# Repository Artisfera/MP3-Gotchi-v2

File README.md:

# MP3-Gotchi v2

A pocket-sized offline MP3 player with a Tamagotchi-style monkey companion, being developed around a custom ESP32-S3 PCB.

## Original version (v1)

## Why?

Have you ever lost signal during a trip and realised that streaming had quietly become your entire music library?

You can store MP3 files on a phone, of course, but carrying a dedicated music player still feels different.

My girlfriend runs into this problem often, so for our anniversary I decided to build her a one-of-a-kind Tamagotchi-style MP3 player. While listening to music, she will also be able to feed and take care of a little monkey companion.

She loves monkeys, so it fits perfectly ✨

## What makes v2 different?

The first MP3-Gotchi proved that the idea could work, but it was built mostly from ready-made development modules. That made the device larger, limited the available hardware choices and left many parts of the design hidden inside separate boards.

Version 2 is being rebuilt around a custom ESP32-S3 PCB. Instead of connecting complete modules together, the main parts of the player are being designed directly into one compact device.

The new version is planned to include:

- offline music playback from a microSD card
- a dedicated stereo DAC and headphone amplifier
- support for wired TRRS headphones and their microphone
- a small internal speaker
- a 96×64 color OLED
- motion sensing
- dual vibration feedback
- a rotary encoder and physical buttons
- USB-C charging and programming
- a rechargeable Li-Ion battery

These are the goals for the complete v2 design. The current HomeFab prototype does not include every planned feature.

## Current status

> [!IMPORTANT]
> MP3-Gotchi v2 is under active hardware development. The version currently available in this repository is **HomeFab v0.1.0**, a reduced PCB design intended for experimental home fabrication. The full version for professional PCB manufacturing is a future development step. The board has not been documented here as manufactured and hardware-tested.

### HomeFab v0.1.0

The HomeFab revision omits microphone support, the dedicated battery over-discharge protection circuit, and the second vibration motor. These are still part of the intended full v2 design.

| Block | Component | HomeFab v0.1.0 status |
| --- | --- | --- |
| USB-C | USB-C receptacle | Included in schematic |
| Battery charger | TP4056 | Included in schematic |
| Battery connection | Li-Ion cell connector | Included in schematic |
| Battery protection | DW01A + FS8205A | Not included in HomeFab |
| 3.3 V buck converter | SC189ZSKTRT | Included in schematic |
| Microcontroller | ESP32-S3-WROOM | Included in schematic |
| Stereo DAC | PCM5102A | Included in schematic |
| Headphone amplifier | TS482IDT | Included in schematic |
| Microphone preamp | TLV9062 | Not included in HomeFab |
| TRRS headphone jack | FC68129 | Included; microphone circuitry omitted |
| microSD socket | ATTEND 112I-TA01 | Included in schematic |
| Rotary encoder | Encoder with push switch | Included in schematic |
| Vibration motors | Mini vibration motor | One included; second omitted |
| 6-axis IMU | MPU6050 | Included in schematic |
| Color OLED | SSD1331, 96×64 | Separate module, connected to main PCB |
| Internal speaker amplifier | PAM8302AAD | Included in schematic |
| Buttons | Two user buttons | Included in schematic |

**Project files:** [HomeFab KiCad project](hardware/MP3-Gotchi-v2_HomeFab/) | [HomeFab BOM (CSV)](hardware/MP3-Gotchi-v2_HomeFab/MP3-Gotchi-v2_HomeFab.csv) | [Historical revision exports](hardware/reversions/)

The BOM is located in the HomeFab directory. It is a working component and purchasing list, not yet a verified manufacturing BOM. Some entries still refer to components omitted from the current HomeFab schematic and need to be reconciled before ordering PCB assembly.

## Development journal

The project is being documented from the first hardware decisions to the final physical build. The journal includes design choices, mistakes, revisions and timelapses from each development session.

[Read the development journal](JOURNAL.md)

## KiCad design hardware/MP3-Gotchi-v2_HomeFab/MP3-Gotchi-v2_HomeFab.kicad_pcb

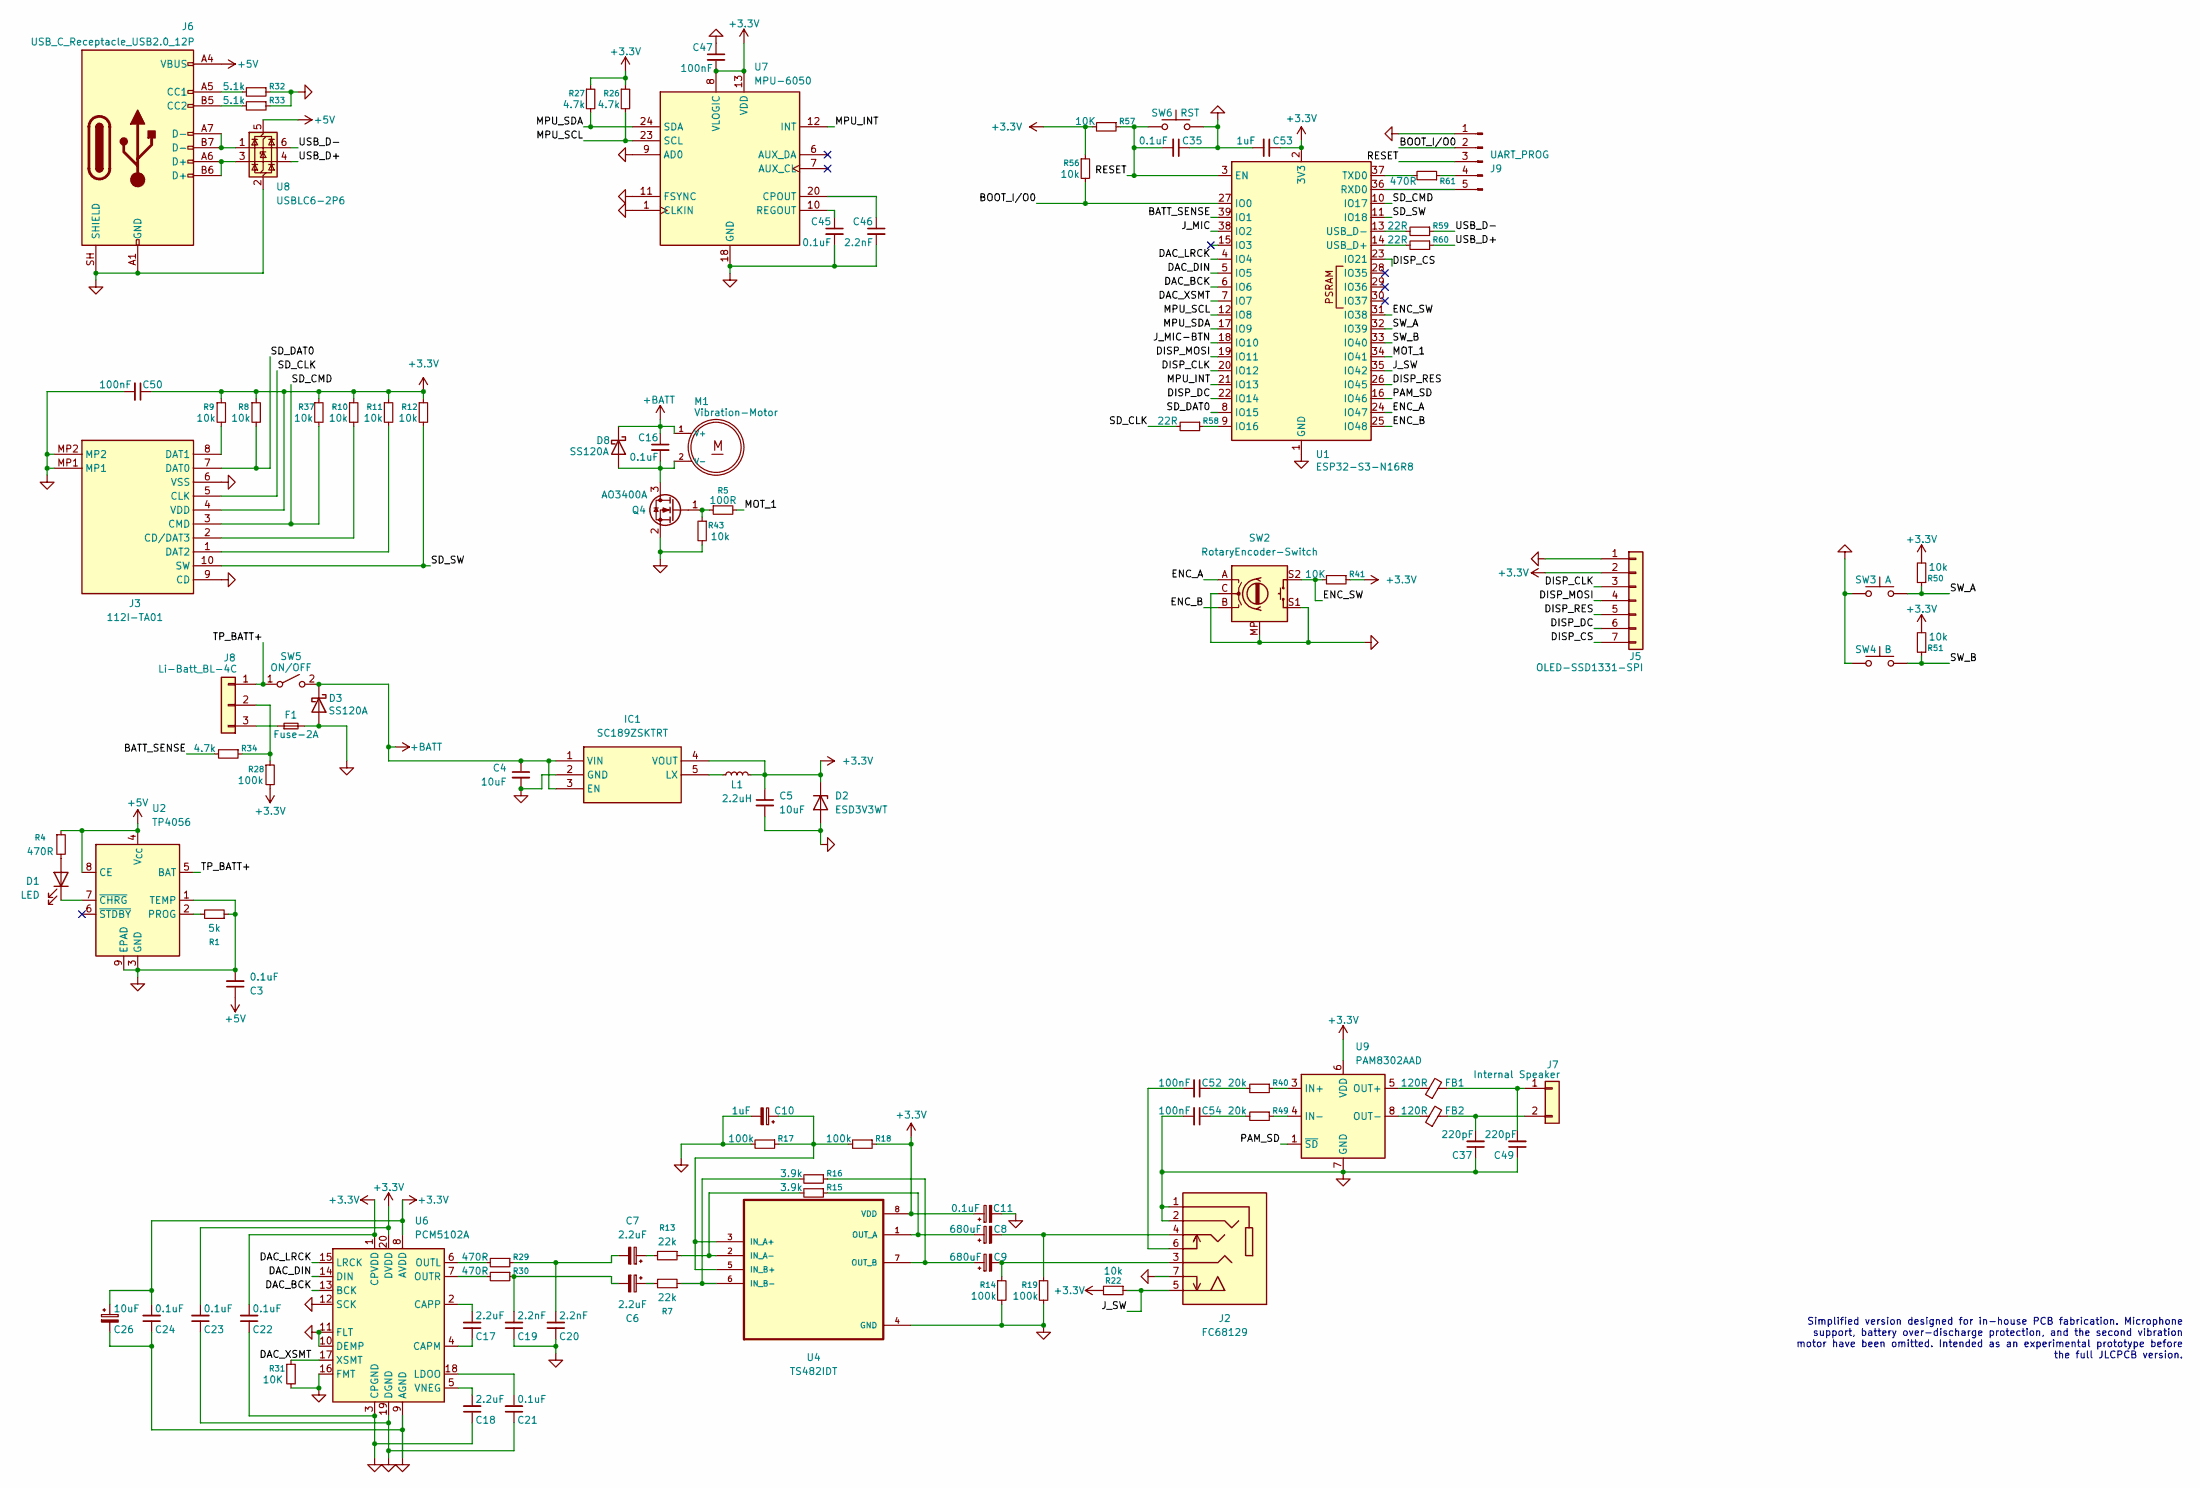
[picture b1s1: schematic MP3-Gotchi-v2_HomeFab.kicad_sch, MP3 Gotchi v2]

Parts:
C3, C11, C16, C21, C22, C23, C24, C45: 0.1uF; C_0402_1005Metric_Pad0.74x0.62mm_HandSolder
C4, C5, C26: 10uF; C_0805_2012Metric_Pad1.18x1.45mm_HandSolder
C6, C7, C17, C18: 2.2uF; C_0805_2012Metric_Pad1.18x1.45mm_HandSolder
C8, C9: 680uF; C_Elec_8x10.2
C10: 1uF; C_0805_2012Metric_Pad1.18x1.45mm_HandSolder
C19, C20, C46: 2.2nF; C_0603_1608Metric_Pad1.08x0.95mm_HandSolder
C35: 0.1uF; C_0805_2012Metric_Pad1.18x1.45mm_HandSolder
C37, C49: 220pF; C_0603_1608Metric_Pad1.08x0.95mm_HandSolder
C47, C50: 100nF; C_0603_1608Metric_Pad1.08x0.95mm_HandSolder
C52, C54: 100nF; C_1206_3216Metric_Pad1.33x1.80mm_HandSolder
C53: 1uF; C_0805_2012Metric
D1: LED; LED_0603_1608Metric_Pad1.05x0.95mm_HandSolder
D2: ESD3V3WT; D_SOD-523
D3, D8: SS120A; D_SMA
F1: Fuse-2A; Fuse_1206_3216Metric_Pad1.42x1.75mm_HandSolder
FB1, FB2: 120R; R_0603_1608Metric_Pad0.98x0.95mm_HandSolder
IC1: SC189ZSKTRT; SOT-753; Manufacturer_Part_Number SC189ZSKTRT
J2: FC68129; AudioJack_Cliff_FC68129
J3: 112I-TA01; ATTEND_112I-TA01; Manufacturer_Part_Number 112I-TA01
J5: OLED-SSD1331-SPI; JST_XH_B7B-XH-A_1x07_P2.50mm_Vertical
J6: USB_C_Receptacle_USB2.0_12P; USB_C_Receptacle_HRO_TYPE-C-31-M-12
J7: Internal Speaker; JST_PH_B2B-PH-K_1x02_P2.00mm_Vertical
J8: Li-Batt_BL-4C; JST_PH_B3B-PH-K_1x03_P2.00mm_Vertical
J9: UART_PROG; PinHeader_1x05_P2.54mm_Vertical
L1: 2.2uH; L_Wuerth_PMFI-252012
M1: Vibration-Motor; JST_PH_B2B-PH-K_1x02_P2.00mm_Vertical
Q4: AO3400A; SOT-23
R1: 5k; R_0603_1608Metric_Pad0.98x0.95mm_HandSolder
R4, R29, R30, R61: 470R; R_0603_1608Metric_Pad0.98x0.95mm_HandSolder
R5: 100R; R_0603_1608Metric_Pad0.98x0.95mm_HandSolder
R7, R13: 22k; R_0603_1608Metric_Pad0.98x0.95mm_HandSolder
R8, R9, R10, R11, R12, R22, R37, R43, R50, R51, R56: 10k; R_0603_1608Metric_Pad0.98x0.95mm_HandSolder
R14, R17, R18, R19, R28: 100k; R_0603_1608Metric_Pad0.98x0.95mm_HandSolder
R15, R16: 3.9k; R_0603_1608Metric_Pad0.98x0.95mm_HandSolder
R26, R27, R34: 4.7k; R_0603_1608Metric_Pad0.98x0.95mm_HandSolder
R31, R41, R57: 10K; R_0603_1608Metric_Pad0.98x0.95mm_HandSolder
R32, R33: 5.1k; R_0603_1608Metric_Pad0.98x0.95mm_HandSolder
R40, R49: 20k; R_0603_1608Metric_Pad0.98x0.95mm_HandSolder
R58, R59, R60: 22R; R_0603_1608Metric_Pad0.98x0.95mm_HandSolder
SW2: RotaryEncoder-Switch; RotaryEncoder_Alps_EC11E-Switch_Vertical_H20mm
SW3: A; Switch_Tactile_SMD_6x6mm
SW4: B; Switch_Tactile_SMD_6x6mm
SW5: ON/OFF; JST_PH_B2B-PH-K_1x02_P2.00mm_Vertical
SW6: RST; SolderJumper-2_P1.3mm_Open_RoundedPad1.0x1.5mm
U1: ESP32-S3-N16R8; ESP32-S3-WROOM-1
U2: TP4056; SOIC-8-1EP_3.9x4.9mm_P1.27mm_EP2.41x3.3mm_ThermalVias
U4: TS482IDT; SOIC-8_3.9x4.9mm_P1.27mm
U6: PCM5102A; TSSOP-20_4.4x6.5mm_P0.65mm
U7: MPU-6050; InvenSense_QFN-24_4x4mm_P0.5mm
U8: USBLC6-2P6; SOT-666
U9: PAM8302AAD; SOIC-8_3.9x4.9mm_P1.27mm

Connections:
+3.3V: C5.1, C11.1, C22.2, C23.2, C24.2, C26.1, C47.2, C50.1, C53.1, D2.1 (K), IC1.4 (VOUT), J3.4 (VDD), J5.2, L1.2, R8.1, R9.1, R10.1, R11.1, R12.1, R18.1, R22.2, R26.1, R27.1, R28.2, R37.1, R41.1, R50.2, R51.2, R56.1, R57.2, U1.2 (3V3), U4.8 (VDD), U6.1 (CPVDD), U6.8 (AVDD), U6.20 (DVDD), U7.8 (VLOGIC), U7.13 (VDD), U9.6 (VDD)
+5V: C3.1, J6.A4 (VBUS), J6.A9 (VBUS), J6.B4 (VBUS), J6.B9 (VBUS), R4.1, U2.4 (V_{CC}), U2.8 (CE), U8.5 (VBUS)
+BATT: C4.1, C16.1, D3.1 (K), D8.1 (K), IC1.1 (VIN), IC1.3 (EN), M1.1 (V+), SW5.2 (B)
/BATT_SENSE: R34.2, U1.39 (IO1)
/BOOT_I/O0: J9.2, R56.2, U1.27 (IO0)
/DAC_BCK: U1.6 (IO6), U6.13 (BCK)
/DAC_DIN: U1.5 (IO5), U6.14 (DIN)
/DAC_LRCK: U1.4 (IO4), U6.15 (LRCK)
/DAC_XSMT: R31.1, U1.7 (IO7), U6.17 (XSMT)
/DISP_CLK: J5.3, U1.20 (IO12)
/DISP_CS: J5.7, U1.23 (IO21)
/DISP_DC: J5.6, U1.22 (IO14)
/DISP_MOSI: J5.4, U1.19 (IO11)
/DISP_RES: J5.5, U1.26 (IO45)
/ENC_A: SW2.A, U1.24 (IO47)
/ENC_B: SW2.B, U1.25 (IO48)
/ENC_SW: R41.2, SW2.S2 (S1), U1.31 (IO38)
/J_MIC: U1.38 (IO2)
/J_MIC-BTN: U1.18 (IO10)
/J_SW: J2.5 (SW_A), R22.1, U1.35 (IO42)
/MOT_1: R5.2, U1.34 (IO41)
/MOT_2: U1.15 (IO3)
/MPU_INT: U1.21 (IO13), U7.12 (INT)
/MPU_SCL: R26.2, U1.12 (IO8), U7.23 (SCL)
/MPU_SDA: R27.2, U1.17 (IO9), U7.24 (SDA)
/PAM_SD: U1.16 (IO46), U9.1 (~SD)
/RESET: C35.2, J9.3, R57.1, SW6.1, U1.3 (EN)
/SD_CLK: J3.5 (CLK), R58.2
/SD_CMD: J3.3 (CMD), R37.2, U1.10 (IO17)
/SD_DAT0: J3.7 (DAT0), R8.2, U1.8 (IO15)
/SD_SW: J3.10 (SW), R12.2, U1.11 (IO18)
/SW_A: R50.1, SW3.2, U1.32 (IO39)
/SW_B: R51.1, SW4.2, U1.33 (IO40)
/TP_BATT+: J8.1 (Pin_3), SW5.1 (A), U2.5 (BAT)
/USB_D+: R60.1, U8.4 (I/O2)
/USB_D-: R59.1, U8.6 (I/O1)
GND: C3.2, C4.2, C5.2, C10.2, C11.2, C18.1, C19.1, C20.1, C21.1, C22.1, C23.1, C24.1, C26.2, C35.1, C37.1, C45.2, C46.2, C47.1, C49.1, C50.2, C53.2, C54.2, D2.2 (A), D3.2 (A), F1.2, IC1.2 (GND), J2.1 (S), J2.2 (R1), J2.7 (SW_B), J3.6 (VSS), J3.9 (CD), J3.MP1, J3.MP2, J5.1, J6.A1 (GND), J6.A12 (GND), J6.B1 (GND), J6.B12 (GND), J6.SH (SHIELD), J9.1, Q4.2 (S), R1.1, R14.2, R17.2, R19.2, R31.2, R32.1, R33.1, R43.2, SW2.C, SW2.MP, SW2.S1 (S2), SW3.1, SW4.1, SW6.2, U1.1 (GND), U1.40 (GND), U1.41 (GND), U2.1 (TEMP), U2.3 (GND), U2.9 (EPAD), U4.4 (GND), U6.3 (CPGND), U6.9 (AGND), U6.10 (DEMP), U6.11 (FLT), U6.12 (SCK), U6.16 (FMT), U6.19 (DGND), U7.1 (CLKIN), U7.9 (AD0), U7.11 (FSYNC), U7.18 (GND), U8.2 (GND), U9.7 (GND)
unnamed: C6.1, R7.2
unnamed: C7.1, R13.2
unnamed: C6.2, C19.2, R30.1
unnamed: C7.2, C20.2, R29.1
unnamed: C52.1, R40.2
unnamed: C54.1, R49.2
unnamed: D1.2 (A), R4.2
unnamed: D1.1 (K), U2.7 (~CHRG)
unnamed: C16.2, D8.2 (A), M1.2 (V-), Q4.3 (D)
unnamed: IC1.5 (LX), L1.1
unnamed: C9.2, J2.3 (R2), R14.1
unnamed: C8.2, J2.4 (T), R19.1
unnamed: C52.2, J2.6 (T_SW)
unnamed: J3.2 (CD/DAT3), R10.2
unnamed: J3.8 (DAT1), R9.2
unnamed: J3.1 (DAT2), R11.2
unnamed: J6.A5 (CC1), R32.2
unnamed: J6.B5 (CC2), R33.2
unnamed: J6.A6 (D+), J6.B6 (D+), U8.3 (I/O2)
unnamed: J6.A7 (D-), J6.B7 (D-), U8.1 (I/O1)
unnamed: C37.2, FB2.2, J7.2 (Pin_1)
unnamed: C49.2, FB1.2, J7.1 (Pin_2)
unnamed: F1.1, J8.3 (Pin_1)
unnamed: J8.2, R28.1, R34.1
unnamed: J9.4, R61.1
unnamed: J9.5, U1.36 (RXD0)
unnamed: Q4.1 (G), R5.1, R43.1
unnamed: R58.1, U1.9 (IO16)
unnamed: R61.2, U1.37 (TXD0)
unnamed: R60.2, U1.14 (USB_D+)
unnamed: R59.2, U1.13 (USB_D-)
unnamed: R1.2, U2.2 (PROG)
unnamed: C10.1, R17.1, R18.2, U4.3 (IN_A+), U4.5 (IN_B+)
unnamed: R13.1, R15.2, U4.2 (IN_A-)
unnamed: R7.1, R16.2, U4.6 (IN_B-)
unnamed: C8.1, R15.1, U4.1 (OUT_A)
unnamed: C9.1, R16.1, U4.7 (OUT_B)
unnamed: C17.1, U6.4 (CAPM)
unnamed: C17.2, U6.2 (CAPP)
unnamed: C21.2, U6.18 (LDOO)
unnamed: R29.2, U6.6 (OUTL)
unnamed: R30.2, U6.7 (OUTR)
unnamed: C18.2, U6.5 (VNEG)
unnamed: C46.1, U7.20 (CPOUT)
unnamed: C45.1, U7.10 (REGOUT)
unnamed: R40.1, U9.3 (IN+)
unnamed: R49.1, U9.4 (IN-)
unnamed: FB1.1, U9.5 (OUT+)
unnamed: FB2.1, U9.8 (OUT-)

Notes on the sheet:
Simplified version designed for in-house PCB fabrication. Microphone support, battery over-discharge protection, and the second vibration motor have been omitted. Intended as an experimental prototype before the full JLCPCB version.

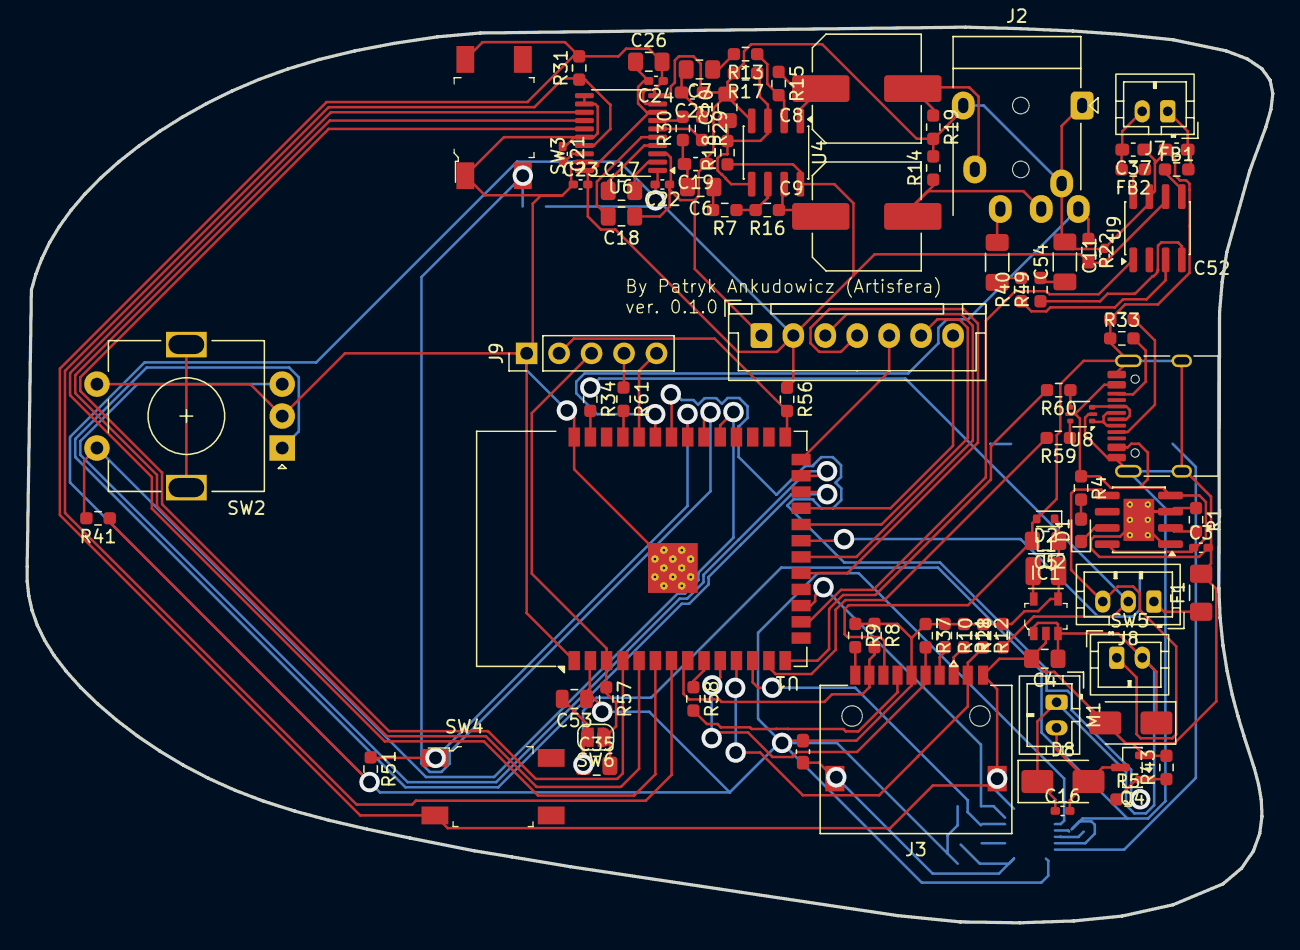
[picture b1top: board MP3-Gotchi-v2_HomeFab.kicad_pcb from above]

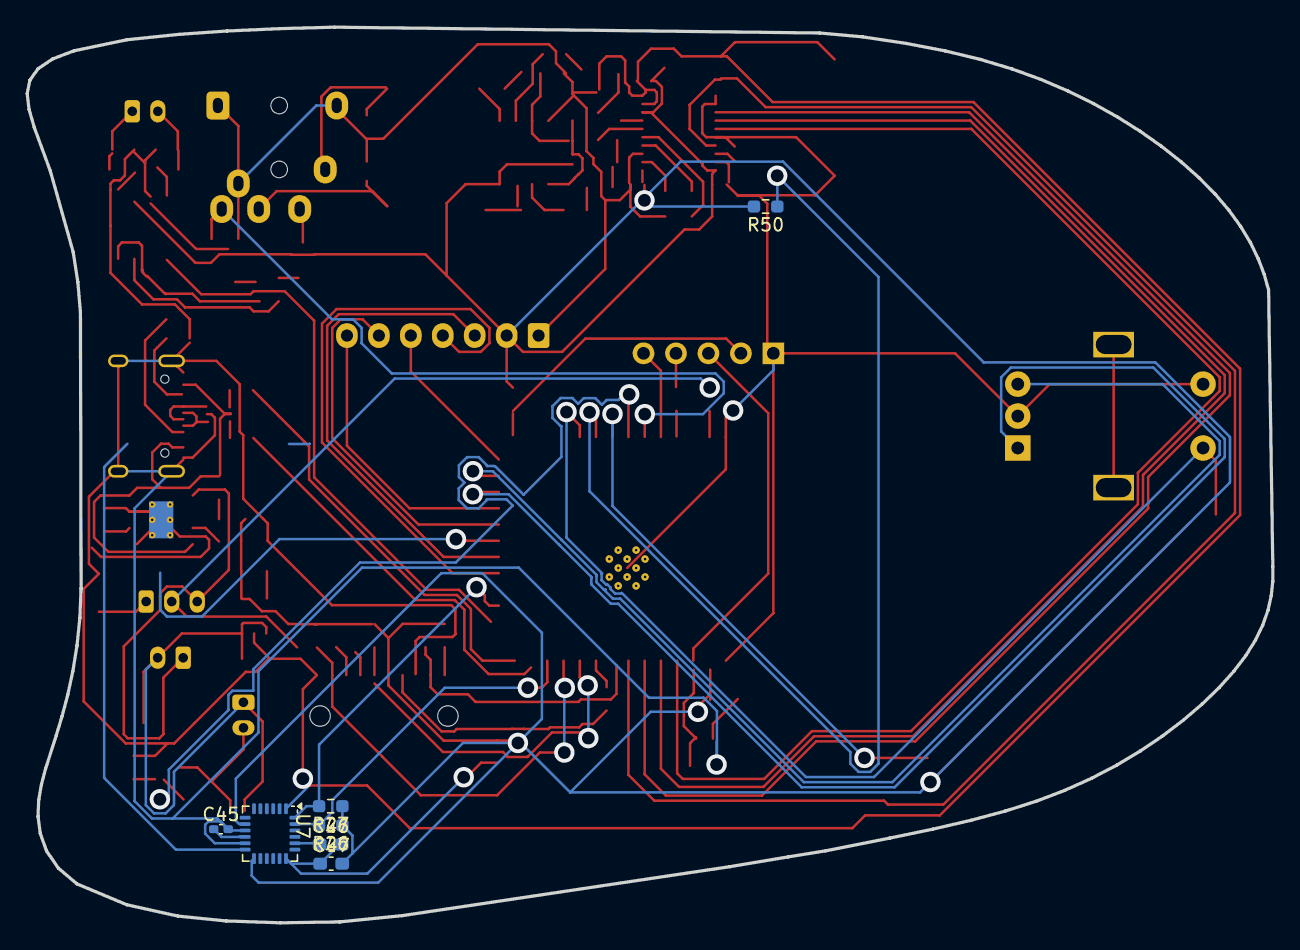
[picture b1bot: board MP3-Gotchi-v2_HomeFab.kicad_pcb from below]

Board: 2 copper layers, 97.5 x 70.1 mm, 98 parts (7 on the bottom side), 83 nets.
